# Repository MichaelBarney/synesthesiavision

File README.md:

# Synesthesia Vision

This project aims to develop pairs of sensory glasses for the visually impaired with IoT and Smart City Capabilities. Through and array of Ultrassonic Sensors, 3D distance information is mapped, sent to a smartphone (using an app), processed and transmitted through 3D sound via headphones. Beyond this sonification feature, other IoT and Smart City Capabilities can be added thanks to the app and the NRF24 module on the glasses.

## More Information
[Youtube Video](https://www.youtube.com/watch?v=zJbMHiAeXqk)

[Facebook Page](https://www.facebook.com/synesthesiavision/?fref=ts)

## Layout of the Project
This project consists of 4 main components:
1. Glasses with Arduino
2. Smartphone App
3. Web Server
4. IoT and Smart City Devices

### Glasses with Arduino
The Arduino Code and PCB layouts for this component are found in the "Glasses_Arduino" folder.

The Arduino used is the Pro_Mini, and it is connected to 3 __modules__:
1. Array of Ultrassonic Sensors
2. Smartphone Comunication Module
3. Remote Comunication Module

For the sonification, the Arduino receives distance information from a __Array of Ultrassonic Sensors__, it filters these information and sends it to the Smartphone through the __Bluetooth Module__.

Both the __NRF24__ and the Smartphone allow Synesthesia Vision to connect with other IoT and Smart City devices.

### Smartphone App
The Android App can be found in the "Synesthesia_APP" folder, the app is developed on Android Studio.

The app assists the sonification feature, supplies the user with audio feedback for the NRF24 triggered features and connects with the Web Server to supply IoT capabilities.

More information about the Smartphone App can be found in the App Folder.

### Web Server and ioT
The NodeJS Server app can be found in the "Server" folder.

The server connects with the smartphone, sendind and receiving requests for features found in the internet, such as retreiving weather information.

More information about the Server App and a list of IoT features can be found in the Server folder.

### Smart City Devices
We aim to construct a porwerfull tool for the visually impaired to interact with day-to-day activities with relative ease. This can be done with the integration with Smart City Devices, such as: bus stops and traffic lights. 

## Authors

* **Michael Barney Jr**
* **Jonathan Kilner**
* **Gilmar Brito**
* **Aida Araújo Ferreira** 

See also the list of [contributors](https://github.com/aidaferreira/synesthesiavision/contributors) who participated in this project.

## License

This project is licensed under the GNU General Public License v3.0 License - see the [LICENSE](LICENSE) file for details.

## Acknowledgments

This project was developped in association with the Pernambuco Institute of Science Education and Technology:

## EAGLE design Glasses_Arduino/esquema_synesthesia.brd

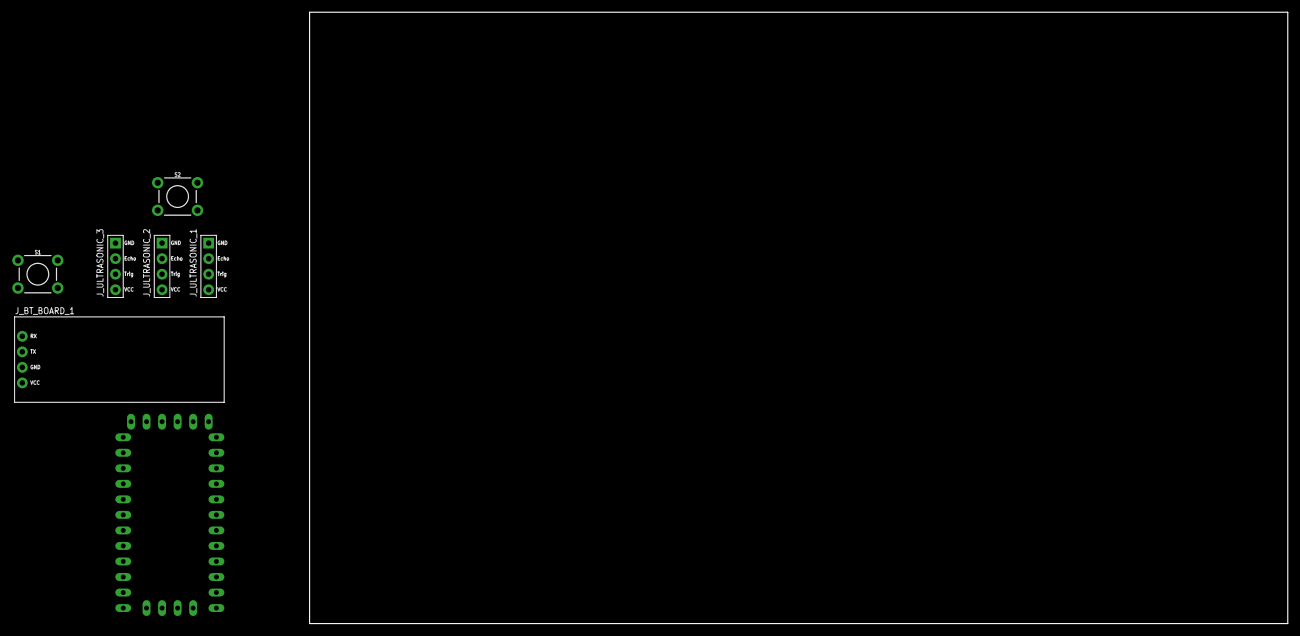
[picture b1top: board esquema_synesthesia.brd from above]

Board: 2 copper layers, 160.0 x 100.0 mm, 7 parts (0 on the bottom side), 12 nets, no tracks yet.

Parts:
J_BT_BOARD_1: BLUETOOTH_BOARD; BT_BOARD_FOOTPRINT
J_ULTRASONIC_1, J_ULTRASONIC_2, J_ULTRASONIC_3: HC-SR04; HC-SR04_FOOTPRINT
S1, S2: MOMENTARY-SWITCH-SPST-PTH-6.0MM; TACTILE_SWITCH_PTH_6.0MM
U$1: PRO-MINI

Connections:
unnamed: J_BT_BOARD_1.VCC, J_ULTRASONIC_1.VCC, J_ULTRASONIC_2.VCC, J_ULTRASONIC_3.VCC, U$1.VCC1
unnamed: J_BT_BOARD_1.GND, J_ULTRASONIC_1.GND, J_ULTRASONIC_2.GND, J_ULTRASONIC_3.GND, S1.1, S2.1, U$1.GND2, U$1.GND3
unnamed: J_ULTRASONIC_3.ECHO, U$1.D4
unnamed: J_ULTRASONIC_3.TRIG, U$1.D5
unnamed: J_ULTRASONIC_2.TRIG, U$1.D7
unnamed: J_ULTRASONIC_2.ECHO, U$1.D6
unnamed: J_ULTRASONIC_1.TRIG, U$1.D9
unnamed: J_ULTRASONIC_1.ECHO, U$1.D8
unnamed: J_BT_BOARD_1.RX, U$1.TX0-1
unnamed: J_BT_BOARD_1.TX, U$1.RX1-1
unnamed: S1.3, U$1.D2
unnamed: S2.3, U$1.D3

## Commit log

2016-11-16 Inicio projeto
2016-11-21 Primeiro Commit
2016-11-23 Corrigido funcionalidades do timer / adicionado EditText para setar manualmente o valor do tempo de cada sensor.
2016-11-23 Adicionado Artigo Cientec
2016-12-19 Corrigido bugs no algoritmo do Android/Arduino
2016-12-21 Corrigido alguns bugs
2017-01-10 Adicionado descrição de itens para facilitar a interação com o Deficiente através do uso do TalkBack
2017-01-23 Adicionado protótitpo de tela acessível
2017-01-23 Adicionado comandos de voz
2017-01-24 Testes com funcionalidade de reconhecimento de voz
2017-01-31 Adicionado reconhecimento de voz por comandos em inglês através da biblioteca pocketsphynx
2017-02-08 Adicionado reconhecimento de voz utilizando a API pocketsphinx e o Google Speech Recognizer, feitos pelo usuário manask88.
2017-02-22 Alteração no Android Manifest
2017-03-01 Pequenas Alterações
2017-03-07 Testes em um novo algoritmo de geração de Áudio 3D
2017-03-09 Novo algoritmo de geração de Áudio 3D
2017-03-10 Adicionado função TTS (Text to Speech) junto com áudio de inicialização do app
2017-03-12 Adicionado permissões necessárias para API 23 ou maior
2017-03-14 Adicionado método de requisição de dados ao webserver (POST) do azure
2017-03-15 Adicionado arquivos de som
2017-03-15 Testes com previsão de tempo com Thread
2017-03-15 Pequenas alterações e linkagem das classes
2017-03-15 Removido arquivos não usados
2017-03-16 Adicionado vibrações no início e na pausa da sonorização
2017-03-16 Create LICENSE
    Added license
2017-03-16 Removido pasta documentacao
2017-03-17 Rename LICENSE to LICENSE,md
2017-03-17 Rename LICENSE,md to LICENSE.md
2017-03-17 Rename LICENSE.md to LICENSE
2017-04-20 Alteracao de repositorio
2017-04-20 Adicionado pasta documentos
2017-04-25 Adicionado content description no layout e corrigido erros de execucao
2017-05-03 Alteração no diretório dos projetos e remoção de versões antigas do APP e dos arquivos do Arduino
2017-05-03 Alterado local dos arquivos do projeto
2017-05-03 Readme Atualizado e criação de um novo Readme na versão em português
2017-05-03 Updated Readme and Readme_PT_BR
2017-05-04 Adicionado novos componentes que serão utilizados no projeto
2017-05-04 Pequenas modificações no aplicativo
2017-05-04 Modificação nos arquivos da descrição do TalkBack
2017-05-04 Adicionado mais material que será utilizado no protótipo dos óculos
2017-05-04 Pequena alteração no Layout
2017-05-04 Corrigido erro na execução do som (Array fora do indice).
2017-05-08 Convertido arquivos de .wav para .ogg
2017-05-08 Convertido arquivos de .wav para .ogg e corrigido "som pulando" na classe soundPool
2017-05-11 Testes com nova geração de áudio 3d e pequenas alterações no layout
2017-05-15 Added GNU header for files
2017-05-23 Relatório PIBIC
2017-06-19 Criacao das pastas Artigos e Relatórios e adição de documentos pertencentes as pastas
2017-06-19 Adicionado gitignore
2017-06-19 Remoção de arquivo do diretório principal
2017-06-21 Correcao no cabecalho dos arquivos xml
2017-06-21 Corrigido bugs no layout em relação ao TalkBack e retirada de código não utilizado da main
2017-10-30 correção readme
2017-10-30 Artigo parcial
2017-10-30 Primeira impressão 3D

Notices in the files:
parts and their libraries:
SparkFun-Switches: Licensing: Creative Commons ShareAlike 4.0 International - https://creativecommons.org/licenses/by-sa/4.0
